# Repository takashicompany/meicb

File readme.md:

# MeiCB

MeiCB(メイシービー)は名刺サイズのキーボード基板です。  
名刺として使えますし、キースイッチやMCUを搭載することで簡易的なマクロパッドとしても利用できます。  
Kicadデーターを公開予定ですので、ご自身のプロフィールやアイコン画像を載せたMeiCBをつくることも可能です。  

(my_meishiから名前を変更しました。)

## 機能の対応状況

### Rev2(my_meishi)

一部の機能は、まだファームウェアの調査中だったり、基板側に拡張が必要なケースがあります。

|機能|対応|詳細|
|:--|:--|:--|
|OLED|？|現在調査中。|
|LED|✗|基板側で追加の実装が必要になる想定。|
|VIA|？|現在調査中。|

## 組み立てに必要な部品

|部品名|個数|備考|
|:--|:--|:--|
|[XIAO RP2040](https://akizukidenshi.com/catalog/g/gM-17044/)|1||
|キースイッチ|4個|取り付けは[Cherry MX互換キースイッチ](https://shop.yushakobo.jp/collections/all-switches/cherry-mx-%E4%BA%92%E6%8F%9B-%E3%82%B9%E3%82%A4%E3%83%83%E3%83%81)と[Kailh Choc v1互換キースイッチ](https://shop.yushakobo.jp/collections/all-switches/kailh-choc-v1%E3%82%B9%E3%82%A4%E3%83%83%E3%83%81)に対応|
|キーキャップ|4個||
|[ゴム足シール](https://shop.yushakobo.jp/collections/all-keyboard-parts/products/a0800ur-01-6)|4個||

## 組み立て方

### 1. 基板の表側にXIAO RP2040を取り付ける

基板の表側右上の箇所にXIAO RP2040を取り付けます。  

XIAO RP2040とピンをはんだ付けします。  
ピンの足がXIAO RP2040の平らな面側に来るようにピンを差しハンダ付けを行います。  

XIAO RP2040をMeiCB基板に差します。  
USBの口が外側を向くようにしてください。  

表面から見たときに、このようになっていれば問題ありません。  

基板とピンをハンダ付けする前にピンをニッパーなどで短く切っておくとハンダ付けがしやすくなり且つ仕上がりが綺麗になります。  

全てのピンをハンダ付けしたら完了です。  

### 2. キースイッチを取り付ける

キースイッチを取り付けます。  

キースイッチをMeiCB基板に配置します。  

キースイッチをマスキングテープなどで固定すると、以降の作業をスムーズに進められます。  

MeiCB基板を裏返したときに、キースイッチの足が出ていることを確認します。  

MeiCB基板とキースイッチをハンダ付けします。  

キーキャップを取り付けます。  

### 3. ファームウェアの書き込み

XIAO RP2040上のUSB口の反対側にある、Bと書かれたボタンを押しながらUSBを繋ぐとファームウェア書き込み状態にできます。

ファームウェアは[こちら](https://github.com/takashicompany/meicb/tree/master/firmware)にございます。

RPI-RP2と書かれたドライブに.uf2をドロップすると、書き込まれます。

ソースコードは[こちら](https://github.com/takashicompany/qmk_firmware/tree/meicb/v1/keyboards/takashicompany/meicb)です。

Remap等への対応は後日予定しております。

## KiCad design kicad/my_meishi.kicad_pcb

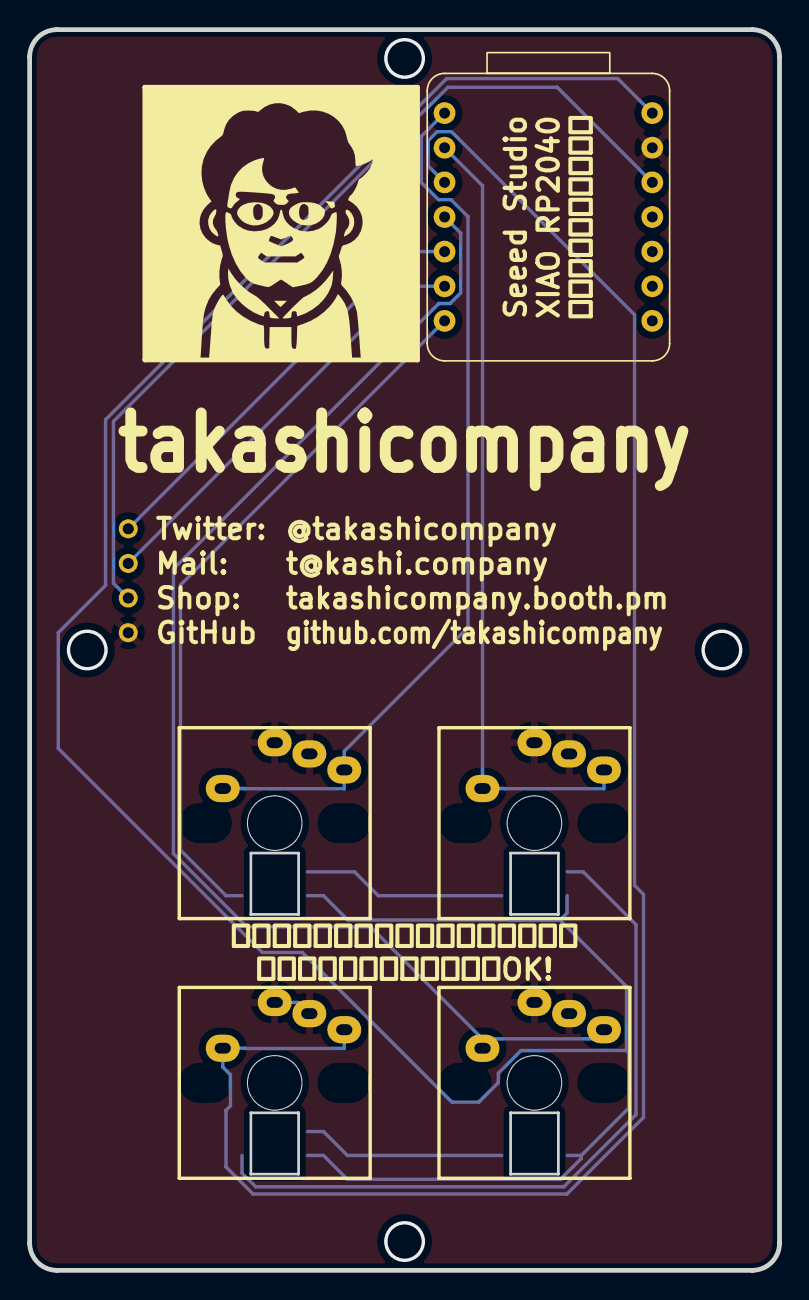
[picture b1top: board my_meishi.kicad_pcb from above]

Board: 2 copper layers, 55.0 x 91.0 mm, 11 parts (0 on the bottom side), 13 nets.

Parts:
Icon: LOGO; icon
LED1, LED2, LED3, LED4: SK6812MINI-E; SK6812MINI_bg
M1: XIAO-RP2040; XIAO-RP2040-inside-only
OL1: OLED; OLED_v2
SW1, SW2, SW3, SW4: SW_Push; CherryMX-MidHeight-Choc_TH_Biased

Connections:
+3V3: M1.12 (3V3), OL1.3 (VCC)
+5V: LED1.1 (VDD), LED2.1 (VDD), LED3.1 (VDD), LED4.1 (VDD), M1.14 (5V)
GND: LED1.3 (VSS), LED2.3 (VSS), LED3.3 (VSS), LED4.3 (VSS), M1.13 (GND), OL1.4 (GND), SW1.2, SW2.2, SW3.2, SW4.2
unnamed: LED1.2 (DOUT), LED2.4 (DIN)
unnamed: LED2.2 (DOUT), LED3.4 (DIN)
unnamed: LED3.2 (DOUT), LED4.4 (DIN)
SCL: M1.6 (D5), OL1.2 (SCL)
SDA: M1.5 (D4), OL1.1 (SDA)
SW1_IN: M1.1 (D0), SW1.1
SW2_IN: M1.2 (D1), SW2.1
SW3_IN: M1.3 (D2), SW3.1
SW4_IN: M1.4 (D3), SW4.1
led: LED1.4 (DIN), M1.7 (D6)

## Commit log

2022-09-17 init commit
2022-09-17 my_meishi
2022-09-17 add image
2022-09-17 rename
2022-09-17 DS Store消す
2022-09-17 画像を修正
2022-09-17 説明を追加
2022-09-17 Kicadを追加
2022-09-18 ファームウェア
